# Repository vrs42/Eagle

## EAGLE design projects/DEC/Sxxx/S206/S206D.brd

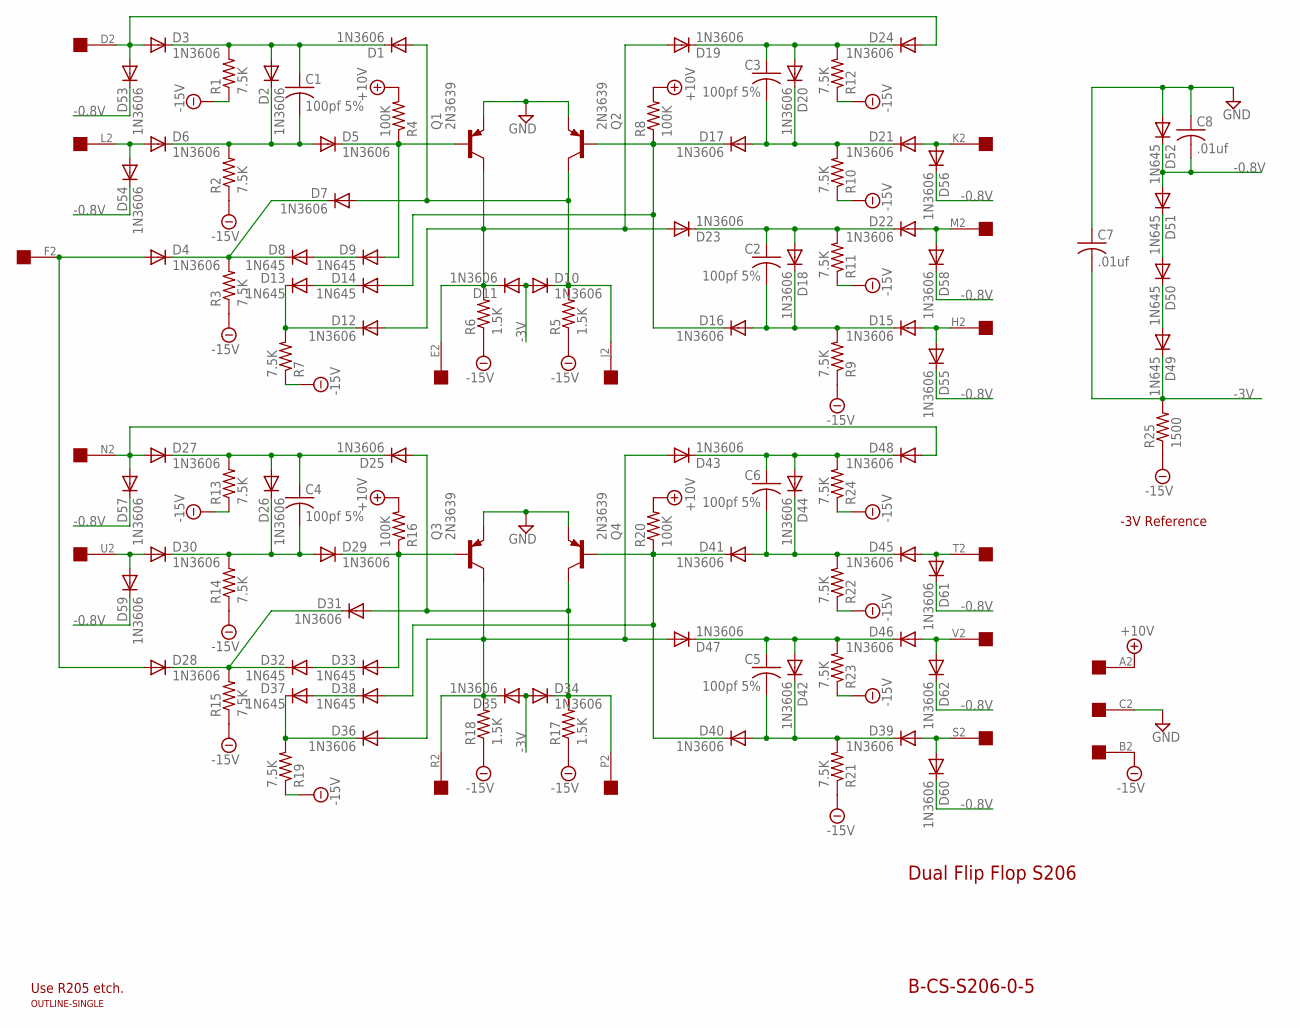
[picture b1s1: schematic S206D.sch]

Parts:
C1, C2, C3, C4, C5, C6: 100pf 5%; C050-025X075
C7, C8: .01uf; C050-025X075
D1, D2, D3, D4, D5, D6, D7, D10, D11, D12, D15, D16, D17, D18, D19, D20, D21, D22, D23, D24, D25, D26, D27, D28, D29, D30, D31, D34, D35, D36, D39, D40, D41, D42, D43, D44, D45, D46, D47, D48, D53, D54, D55, D56, D57, D58, D59, D60, D61, D62: 1N3606; DO35-10
D8, D9, D13, D14, D32, D33, D37, D38, D49, D50, D51, D52: 1N645; DO35-10
Q1, Q2, Q3, Q4: 2N3639; TO39
R1, R2, R3, R7, R9, R10, R11, R12, R13, R14, R15, R19, R21, R22, R23, R24: 7.5K; 0207/10
R4, R8, R16, R20: 100K; 0207/10
R5, R6, R17, R18: 1.5K; 0207/10
R25: 1500; 0207/10
U$1: OUTLINE-SINGLE; SINGLE
U$2: EDGE-1; EDGE-CON1

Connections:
+10V: R4.2, R8.2, R16.2, R20.2, U$2.A2
-0.8V: C8.2, D51.A, D52.C, D53.C, D54.C, D55.C, D56.C, D57.C, D58.C, D59.C, D60.C, D61.C, D62.C
-3V: C7.2, D10.A, D11.A, D34.A, D35.A, D49.C, R25.2
-15V: R1.1, R2.1, R3.1, R5.1, R6.1, R7.1, R9.1, R10.1, R11.1, R12.1, R13.1, R14.1, R15.1, R17.1, R18.1, R19.1, R21.1, R22.1, R23.1, R24.1, R25.1, U$2.B2
E: D11.C, D12.A, D19.A, D23.A, Q1.3 (C), R6.2, U$2.E2
GND: C7.1, C8.1, D52.A, Q1.1 (E), Q2.1 (E), Q3.1 (E), Q4.1 (E), U$2.C2
J: D1.A, D7.A, D10.C, Q2.3 (C), R5.2, U$2.J2
unnamed: C4.1, D25.C, D26.A, D27.C, R13.2
unnamed: C3.1, D19.C, D20.A, D24.C, R12.2
unnamed: C1.2, D2.C, D5.A, D6.C, R2.2
unnamed: D3.A, D24.A, D53.A, U$2.D2
unnamed: D6.A, D54.A, U$2.L2
unnamed: D13.A, D14.C
unnamed: D32.A, D33.C
unnamed: C3.2, D17.A, D20.C, D21.C, R10.2
unnamed: D4.C, D7.C, D8.C, R3.2
unnamed: D4.A, D28.A, U$2.F2
unnamed: D21.A, D56.A, U$2.K2
unnamed: D12.C, D13.C, R7.2
unnamed: D50.A, D51.C
unnamed: D5.C, D9.A, Q1.2 (B), R4.1
unnamed: C4.2, D26.C, D29.A, D30.C, R14.2
unnamed: D49.A, D50.C
unnamed: D14.A, D16.C, D17.C, Q2.2 (B), R8.1
unnamed: D30.A, D59.A, U$2.U2
unnamed: D28.C, D31.C, D32.C, R15.2
unnamed: D29.C, D33.A, Q3.2 (B), R16.1
unnamed: C1.1, D1.C, D2.A, D3.C, R1.2
unnamed: D8.A, D9.C
unnamed: C6.1, D43.C, D44.A, D48.C, R24.2
unnamed: D37.A, D38.C
unnamed: C6.2, D41.A, D44.C, D45.C, R22.2
unnamed: D45.A, D61.A, U$2.T2
unnamed: C2.1, D18.A, D22.C, D23.C, R11.2
unnamed: D38.A, D40.C, D41.C, Q4.2 (B), R20.1
unnamed: D22.A, D58.A, U$2.M2
unnamed: C2.2, D15.C, D16.A, D18.C, R9.2
unnamed: D15.A, D55.A, U$2.H2
unnamed: D36.C, D37.C, R19.2
unnamed: C5.1, D42.A, D46.C, D47.C, R23.2
unnamed: D46.A, D62.A, U$2.V2
unnamed: C5.2, D39.C, D40.A, D42.C, R21.2
unnamed: D39.A, D60.A, U$2.S2
unnamed: D27.A, D48.A, D57.A, U$2.N2
P: D25.A, D31.A, D34.C, Q4.3 (C), R17.2, U$2.P2
R: D35.C, D36.A, D43.A, D47.A, Q3.3 (C), R18.2, U$2.R2

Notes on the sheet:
Dual Flip Flop S206
B-CS-S206-0-5
-3V Reference
Use R205 etch.

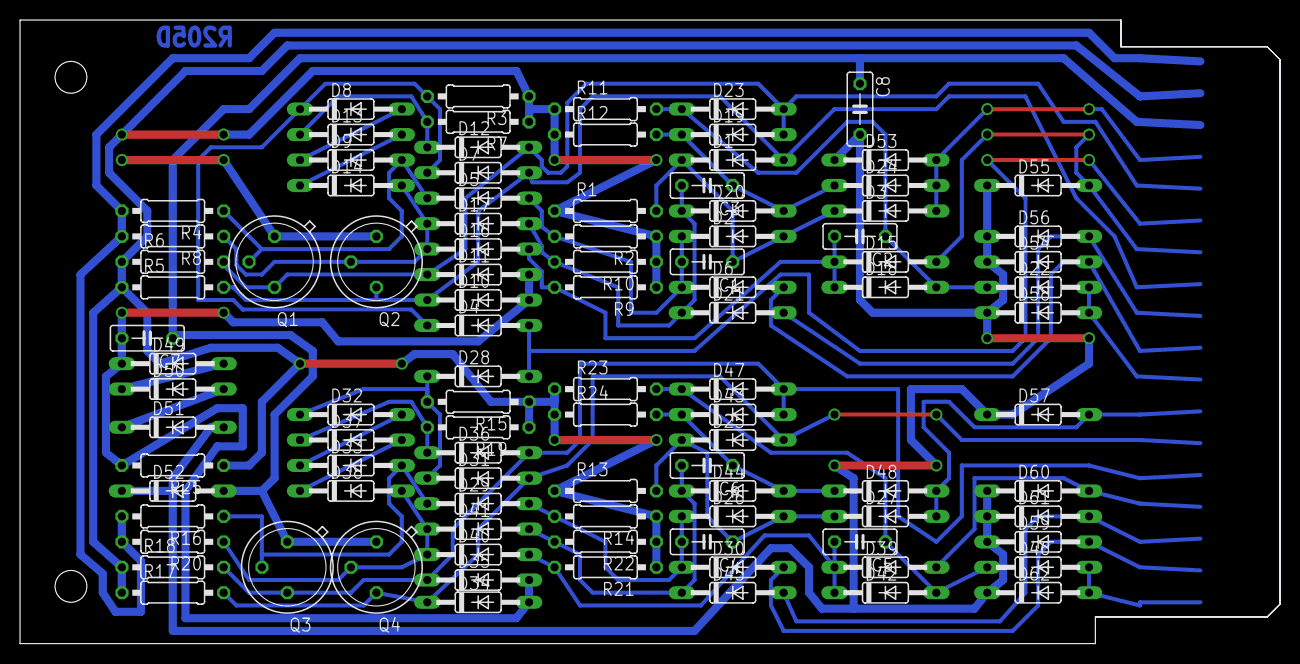
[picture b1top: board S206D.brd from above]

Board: 2 copper layers, 125.7 x 62.2 mm, 101 parts (0 on the bottom side), 46 nets.

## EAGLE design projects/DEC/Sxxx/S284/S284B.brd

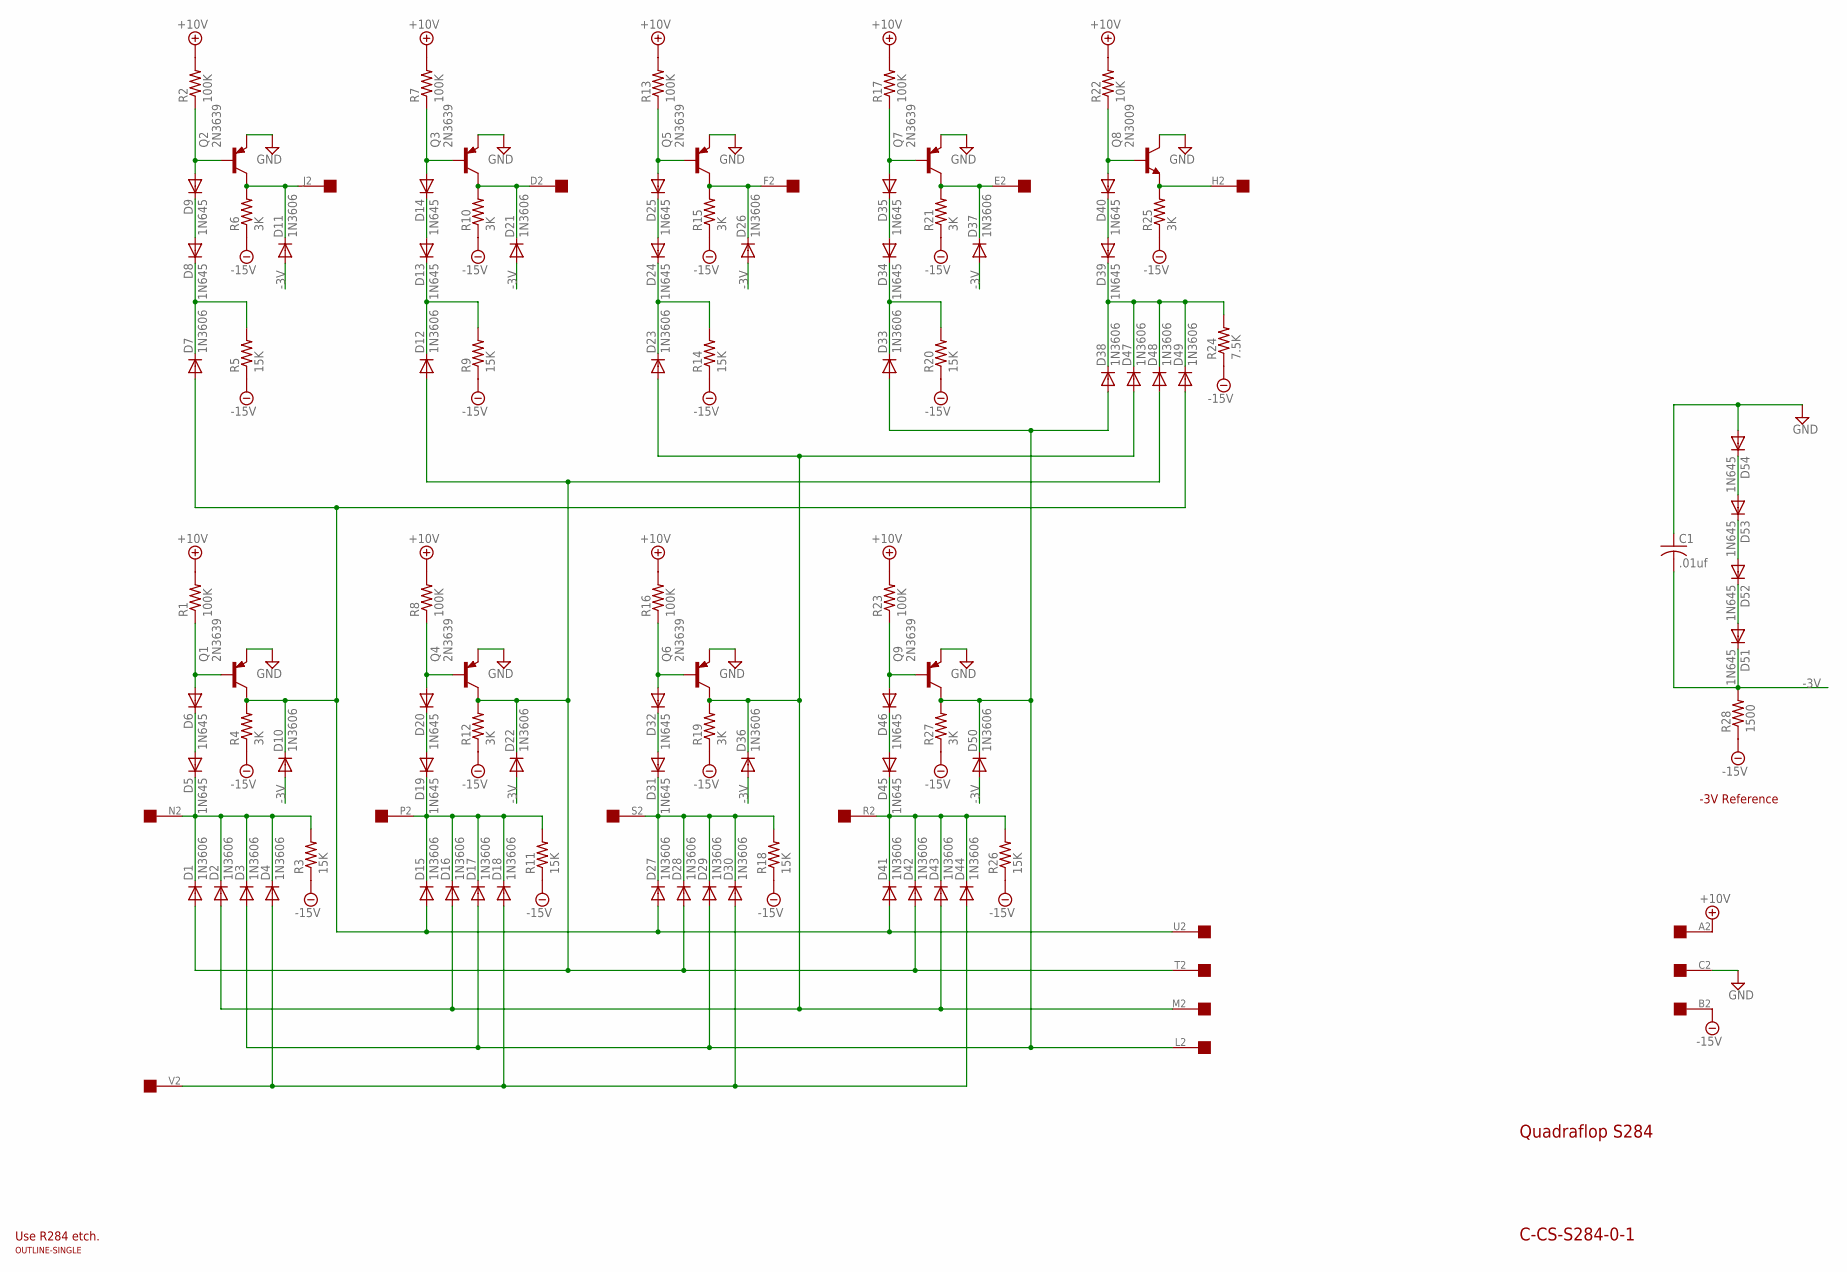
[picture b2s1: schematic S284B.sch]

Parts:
C1: .01uf; C050-025X075
D1, D2, D3, D4, D7, D10, D11, D12, D15, D16, D17, D18, D21, D22, D23, D26, D27, D28, D29, D30, D33, D36, D37, D38, D41, D42, D43, D44, D47, D48, D49, D50: 1N3606; DO35-10
D5, D6, D8, D9, D13, D14, D19, D20, D24, D25, D31, D32, D34, D35, D39, D40, D45, D46, D51, D52, D53, D54: 1N645; DO35-10
Q1, Q2, Q3, Q4, Q5, Q6, Q7, Q9: 2N3639; TO39
Q8: 2N3009; TO5
R1, R2, R7, R8, R13, R16, R17, R23: 100K; 0207/10
R3, R5, R9, R11, R14, R18, R20, R26: 15K; 0207/10
R4, R6, R10, R12, R15, R19, R21, R25, R27: 3K; 0207/10
R22: 10K; 0207/10
R24: 7.5K; 0207/10
R28: 1500; 0207/10
U$1: OUTLINE-SINGLE; SINGLE
U$2: EDGE-1; EDGE-CON1

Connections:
+10V: R1.2, R2.2, R7.2, R8.2, R13.2, R16.2, R17.2, R22.2, R23.2, U$2.A2
-0.8V: D53.A, D54.C
-3V: C1.2, D10.A, D11.A, D21.A, D22.A, D26.A, D36.A, D37.A, D50.A, D51.C, R28.2
-15V: R3.1, R4.1, R5.1, R6.1, R9.1, R10.1, R11.1, R12.1, R14.1, R15.1, R18.1, R19.1, R20.1, R21.1, R24.1, R25.1, R26.1, R27.1, R28.1, U$2.B2
GND: C1.1, D54.A, Q1.1 (E), Q2.1 (E), Q3.1 (E), Q4.1 (E), Q5.1 (E), Q6.1 (E), Q7.1 (E), Q8.3 (C), Q9.1 (E), U$2.C2
L: D3.A, D17.A, D29.A, D33.A, D38.A, D50.C, Q9.3 (C), R27.2, U$2.L2
M: D2.A, D16.A, D23.A, D36.C, D43.A, D47.A, Q6.3 (C), R19.2, U$2.M2
N: D1.C, D2.C, D3.C, D4.C, D5.C, R3.2, U$2.N2
unnamed: D20.A, Q4.2 (B), R8.1
unnamed: D19.A, D20.C
unnamed: D7.A, D10.C, D15.A, D27.A, D41.A, D49.A, Q1.3 (C), R4.2, U$2.U2
unnamed: D7.C, D8.C, R5.2
unnamed: D1.A, D12.A, D22.C, D28.A, D42.A, D48.A, Q4.3 (C), R12.2, U$2.T2
unnamed: D12.C, D13.C, R9.2
unnamed: D13.A, D14.C
unnamed: D8.A, D9.C
unnamed: D21.C, Q3.3 (C), R10.2, U$2.D2
unnamed: D52.A, D53.C
unnamed: D11.C, Q2.3 (C), R6.2, U$2.J2
unnamed: D14.A, Q3.2 (B), R7.1
unnamed: D51.A, D52.C
unnamed: D27.C, D28.C, D29.C, D30.C, D31.C, R18.2, U$2.S2
unnamed: D32.A, Q6.2 (B), R16.1
unnamed: D4.A, D18.A, D30.A, D44.A, U$2.V2
unnamed: D31.A, D32.C
unnamed: D9.A, Q2.2 (B), R2.1
unnamed: D38.C, D39.C, D47.C, D48.C, D49.C, R24.2
unnamed: D23.C, D24.C, R14.2
unnamed: D24.A, D25.C
unnamed: D26.C, Q5.3 (C), R15.2, U$2.F2
unnamed: D25.A, Q5.2 (B), R13.1
unnamed: D41.C, D42.C, D43.C, D44.C, D45.C, R26.2, U$2.R2
unnamed: D6.A, Q1.2 (B), R1.1
unnamed: D46.A, Q9.2 (B), R23.1
unnamed: D5.A, D6.C
unnamed: D45.A, D46.C
unnamed: D40.A, Q8.2 (B), R22.1
unnamed: D33.C, D34.C, R20.2
unnamed: D34.A, D35.C
unnamed: D37.C, Q7.3 (C), R21.2, U$2.E2
unnamed: D35.A, Q7.2 (B), R17.1
unnamed: D39.A, D40.C
unnamed: Q8.1 (E), R25.2, U$2.H2
P: D15.C, D16.C, D17.C, D18.C, D19.C, R11.2, U$2.P2

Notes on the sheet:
Quadraflop S284
C-CS-S284-0-1
-3V Reference
Use R284 etch.

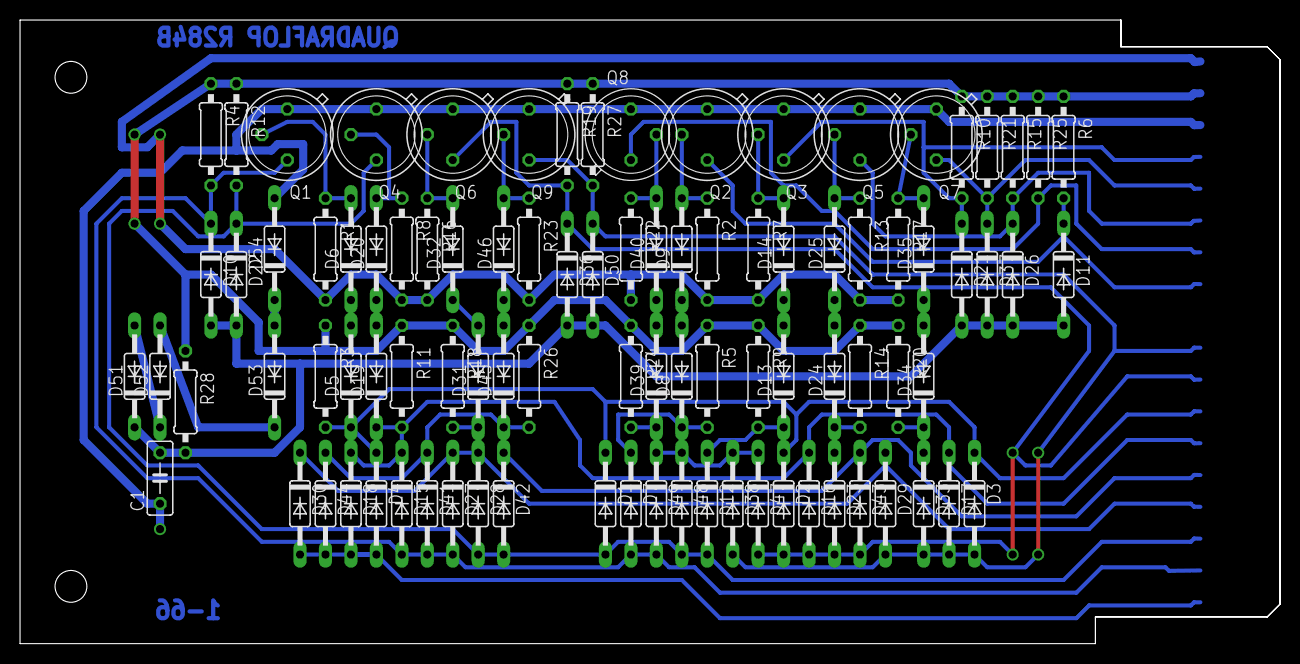
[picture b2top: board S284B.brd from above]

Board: 2 copper layers, 125.7 x 62.2 mm, 94 parts (0 on the bottom side), 44 nets.

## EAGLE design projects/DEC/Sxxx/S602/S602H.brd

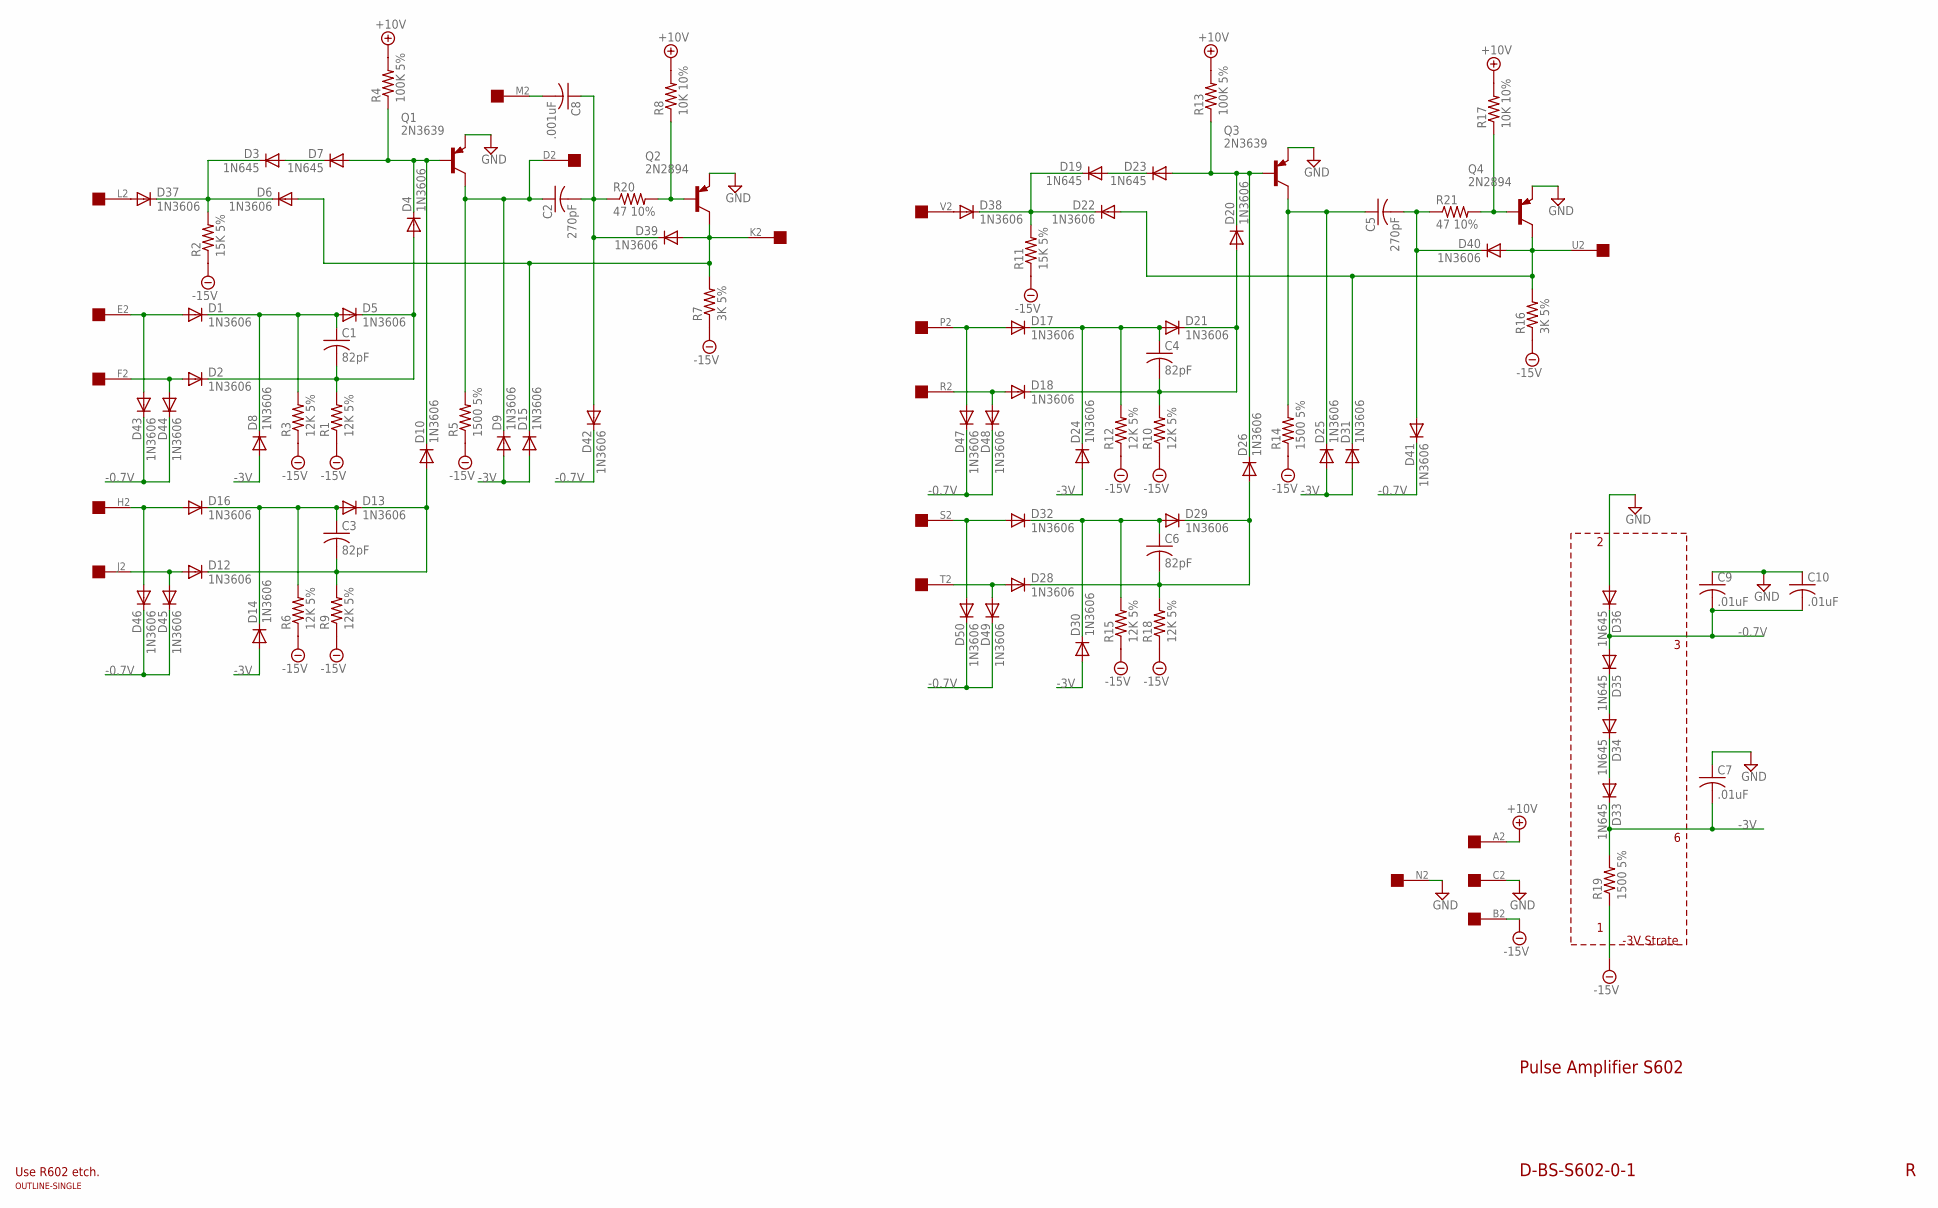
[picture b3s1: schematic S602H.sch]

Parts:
C1, C3, C4, C6: 82pF; C050-025X075
C2, C5: 270pF; C050-025X075
C7: .01uF; C075-032X103
C8: .001uF; C050-025X075
C9, C10: .01uF; C050-025X075
D1, D2, D4, D5, D6, D8, D9, D10, D12, D13, D14, D15, D16, D17, D18, D20, D21, D22, D24, D25, D26, D28, D29, D30, D31, D32, D37, D38, D39, D40, D41, D42, D43, D44, D45, D46, D47, D48, D49, D50: 1N3606; DO35-10
D3, D7, D19, D23, D33, D34, D35, D36: 1N645; DO35-10
Q1, Q3: 2N3639; TO39
Q2, Q4: 2N2894; TO39
R1, R3, R6, R9, R10, R12, R15, R18: 12K 5%; 0207/10
R2, R11: 15K 5%; 0207/10
R4, R13: 100K 5%; 0207/10
R5, R14, R19: 1500 5%; 0207/10
R7, R16: 3K 5%; 0207/10
R8, R17: 10K 10%; 0207/10
R20, R21: 47 10%; 0207/10
U$1: OUTLINE-SINGLE; SINGLE
U$2: EDGE-1; EDGE-CON1

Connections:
+10V: R4.2, R8.2, R13.2, R17.2, U$2.A2
-0.7V: C9.2, C10.2, D35.A, D36.C, D41.C, D42.C, D43.C, D44.C, D45.C, D46.C, D47.C, D48.C, D49.C, D50.C
-3V: C7.2, D8.A, D9.A, D14.A, D15.A, D24.A, D25.A, D30.A, D31.A, D33.C, R19.2
-15V: R1.1, R2.1, R3.1, R5.1, R6.1, R7.1, R9.1, R10.1, R11.1, R12.1, R14.1, R15.1, R16.1, R18.1, R19.1, U$2.B2
GND: C7.1, C9.1, C10.1, D36.A, Q1.1 (E), Q2.1 (E), Q3.1 (E), Q4.1 (E), U$2.C2, U$2.N2
unnamed: D37.A, U$2.L2
unnamed: D3.C, D6.C, D37.C, R2.2
unnamed: D1.A, D43.A, U$2.E2
unnamed: D2.A, D44.A, U$2.F2
unnamed: C1.1, D1.C, D5.A, D8.C, R3.2
unnamed: C1.2, D2.C, D4.A, D5.C, R1.2
unnamed: D3.A, D7.C
unnamed: D34.A, D35.C
unnamed: D33.A, D34.C
unnamed: D4.C, D7.A, D10.C, Q1.2 (B), R4.1
unnamed: C2.1, D9.C, Q1.3 (C), R5.2, U$2.D2
unnamed: C2.2, C8.1, D39.C, D42.A, R20.1
unnamed: Q2.2 (B), R8.1, R20.2
unnamed: D6.A, D15.C, D39.A, Q2.3 (C), R7.2, U$2.K2
unnamed: D16.A, D46.A, U$2.H2
unnamed: D12.A, D45.A, U$2.J2
unnamed: C3.1, D13.A, D14.C, D16.C, R6.2
unnamed: C3.2, D10.A, D12.C, D13.C, R9.2
unnamed: D17.A, D47.A, U$2.P2
unnamed: D18.A, D48.A, U$2.R2
unnamed: C4.1, D17.C, D21.A, D24.C, R12.2
unnamed: C4.2, D18.C, D20.A, D21.C, R10.2
unnamed: D38.A, U$2.V2
unnamed: D19.C, D22.C, D38.C, R11.2
unnamed: D19.A, D23.C
unnamed: D20.C, D23.A, D26.C, Q3.2 (B), R13.1
unnamed: C5.1, D25.C, Q3.3 (C), R14.2
unnamed: C5.2, D40.C, D41.A, R21.1
unnamed: Q4.2 (B), R17.1, R21.2
unnamed: D22.A, D31.C, D40.A, Q4.3 (C), R16.2, U$2.U2
unnamed: D32.A, D50.A, U$2.S2
unnamed: D28.A, D49.A, U$2.T2
unnamed: C6.1, D29.A, D30.C, D32.C, R15.2
unnamed: C6.2, D26.A, D28.C, D29.C, R18.2
unnamed: C8.2, U$2.M2

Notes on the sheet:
Pulse Amplifier S602
D-BS-S602-0-1
-3V Strate
Use R602 etch.

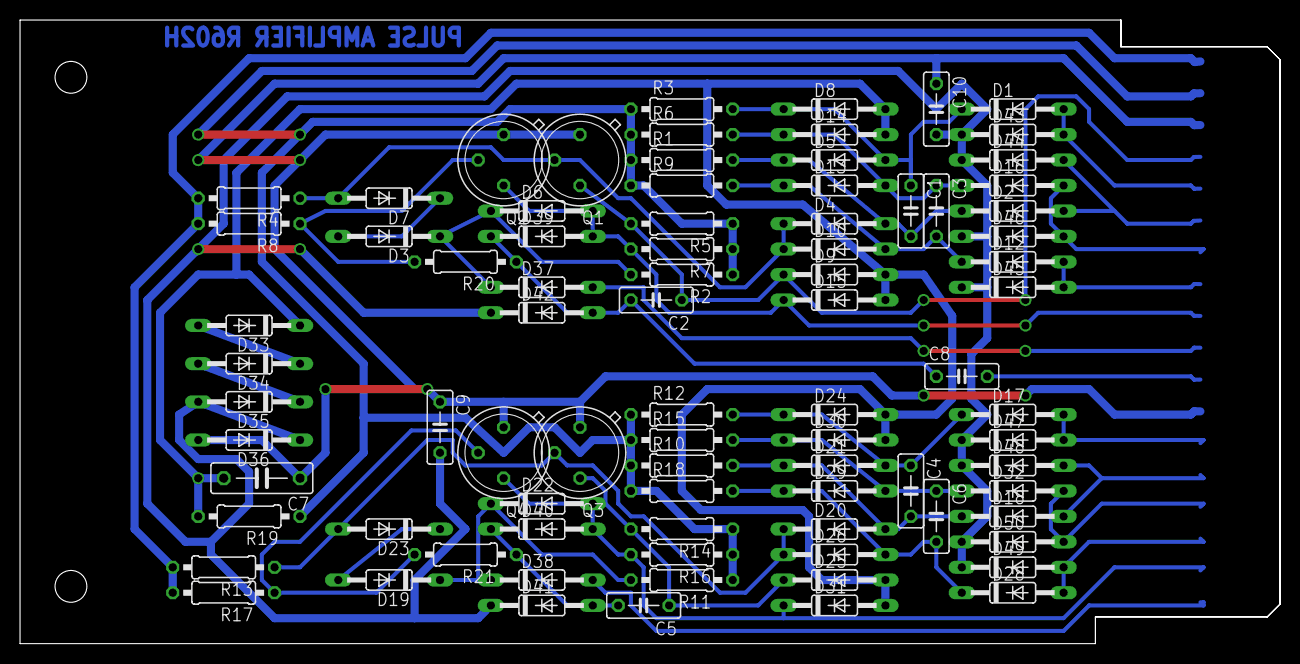
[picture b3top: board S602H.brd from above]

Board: 2 copper layers, 125.7 x 62.2 mm, 85 parts (0 on the bottom side), 40 nets.

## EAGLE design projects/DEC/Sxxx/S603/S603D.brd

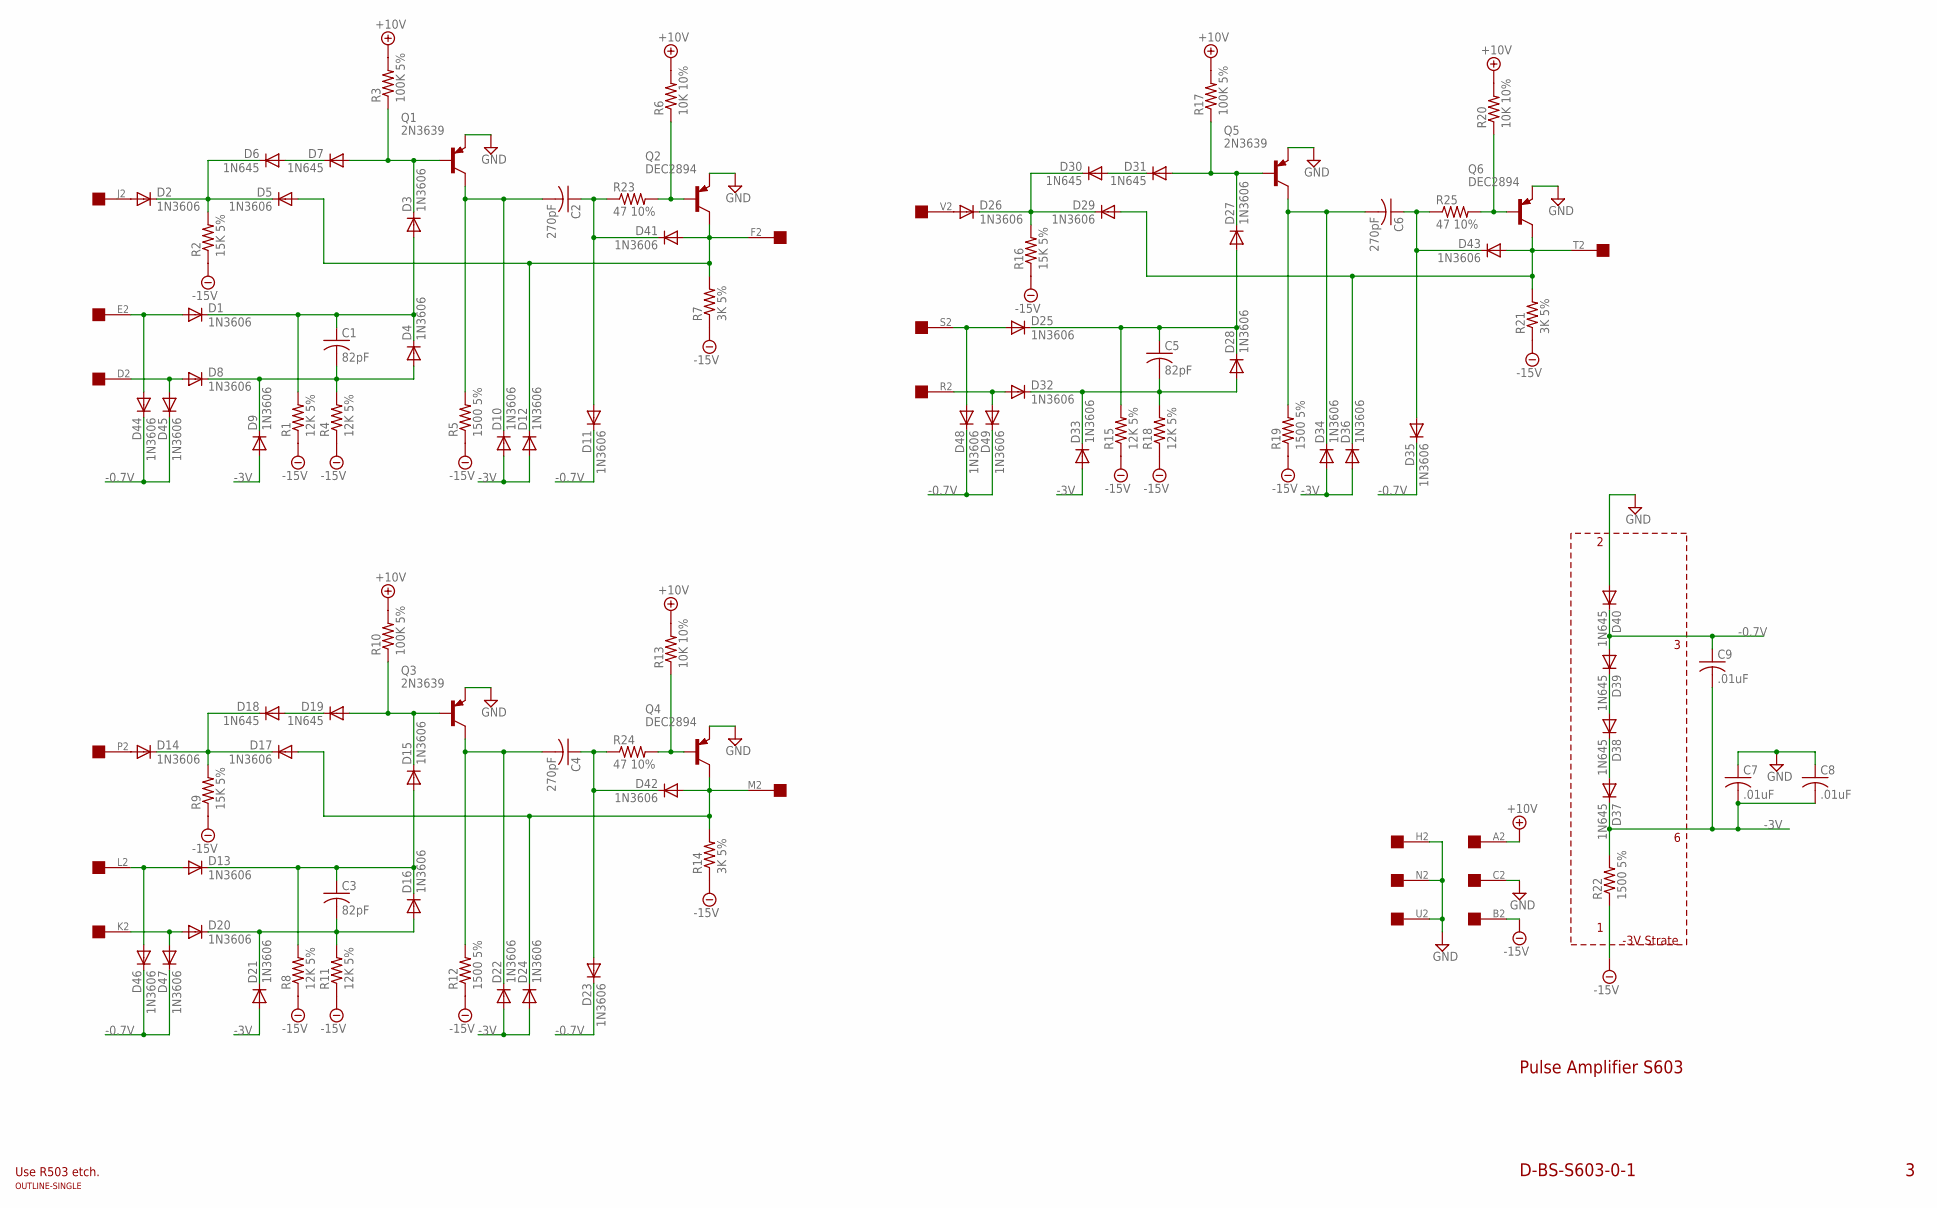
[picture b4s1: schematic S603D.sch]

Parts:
C1, C3, C5: 82pF; C050-025X075
C2, C4, C6: 270pF; C050-025X075
C7, C8, C9: .01uF; C050-025X075
D1, D2, D3, D4, D5, D8, D9, D10, D11, D12, D13, D14, D15, D16, D17, D20, D21, D22, D23, D24, D25, D26, D27, D28, D29, D32, D33, D34, D35, D36, D41, D42, D43, D44, D45, D46, D47, D48, D49: 1N3606; DO35-10
D6, D7, D18, D19, D30, D31, D37, D38, D39, D40: 1N645; DO35-10
Q1, Q3, Q5: 2N3639; TO39
Q2, Q4, Q6: DEC2894; TO39
R1, R4, R8, R11, R15, R18: 12K 5%; 0207/10
R2, R9, R16: 15K 5%; 0207/10
R3, R10, R17: 100K 5%; 0207/10
R5, R12, R19, R22: 1500 5%; 0207/10
R6, R13, R20: 10K 10%; 0207/10
R7, R14, R21: 3K 5%; 0207/10
R23, R24, R25: 47 10%; 0207/10
U$1: OUTLINE-SINGLE; SINGLE
U$2: EDGE-1; EDGE-CON1

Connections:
+10V: R3.2, R6.2, R10.2, R13.2, R17.2, R20.2, U$2.A2
-0.7V: C9.1, D11.C, D23.C, D35.C, D39.A, D40.C, D44.C, D45.C, D46.C, D47.C, D48.C, D49.C
-3V: C7.2, C8.2, C9.2, D9.A, D10.A, D12.A, D21.A, D22.A, D24.A, D33.A, D34.A, D36.A, D37.C, R22.2
-15V: R1.1, R2.1, R4.1, R5.1, R7.1, R8.1, R9.1, R11.1, R12.1, R14.1, R15.1, R16.1, R18.1, R19.1, R21.1, R22.1, U$2.B2
GND: C7.1, C8.1, D40.A, Q1.1 (E), Q2.1 (E), Q3.1 (E), Q4.1 (E), Q5.1 (E), Q6.1 (E), U$2.C2, U$2.H2, U$2.N2, U$2.U2
unnamed: D2.A, U$2.J2
unnamed: D2.C, D5.C, D6.C, R2.2
unnamed: D1.A, D44.A, U$2.E2
unnamed: D8.A, D45.A, U$2.D2
unnamed: C1.1, D1.C, D3.A, D4.C, R1.2
unnamed: C1.2, D4.A, D8.C, D9.C, R4.2
unnamed: D6.A, D7.C
unnamed: D38.A, D39.C
unnamed: D37.A, D38.C
unnamed: D3.C, D7.A, Q1.2 (B), R3.1
unnamed: C2.2, D10.C, Q1.3 (C), R5.2
unnamed: C2.1, D11.A, D41.C, R23.1
unnamed: Q2.2 (B), R6.1, R23.2
unnamed: D5.A, D12.C, D41.A, Q2.3 (C), R7.2, U$2.F2
unnamed: D13.A, D46.A, U$2.L2
unnamed: D20.A, D47.A, U$2.K2
unnamed: C3.1, D13.C, D15.A, D16.C, R8.2
unnamed: C3.2, D16.A, D20.C, D21.C, R11.2
unnamed: D25.A, D48.A, U$2.S2
unnamed: D32.A, D49.A, U$2.R2
unnamed: C5.1, D25.C, D27.A, D28.C, R15.2
unnamed: C5.2, D28.A, D32.C, D33.C, R18.2
unnamed: D26.A, U$2.V2
unnamed: D26.C, D29.C, D30.C, R16.2
unnamed: D30.A, D31.C
unnamed: D27.C, D31.A, Q5.2 (B), R17.1
unnamed: C6.2, D34.C, Q5.3 (C), R19.2
unnamed: C6.1, D35.A, D43.C, R25.1
unnamed: Q6.2 (B), R20.1, R25.2
unnamed: D29.A, D36.C, D43.A, Q6.3 (C), R21.2, U$2.T2
unnamed: D14.A, U$2.P2
unnamed: D14.C, D17.C, D18.C, R9.2
unnamed: D18.A, D19.C
unnamed: D15.C, D19.A, Q3.2 (B), R10.1
unnamed: C4.2, D22.C, Q3.3 (C), R12.2
unnamed: C4.1, D23.A, D42.C, R24.1
unnamed: Q4.2 (B), R13.1, R24.2
unnamed: D17.A, D24.C, D42.A, Q4.3 (C), R14.2, U$2.M2

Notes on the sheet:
Pulse Amplifier S603
D-BS-S603-0-1
-3V Strate
Use R503 etch.

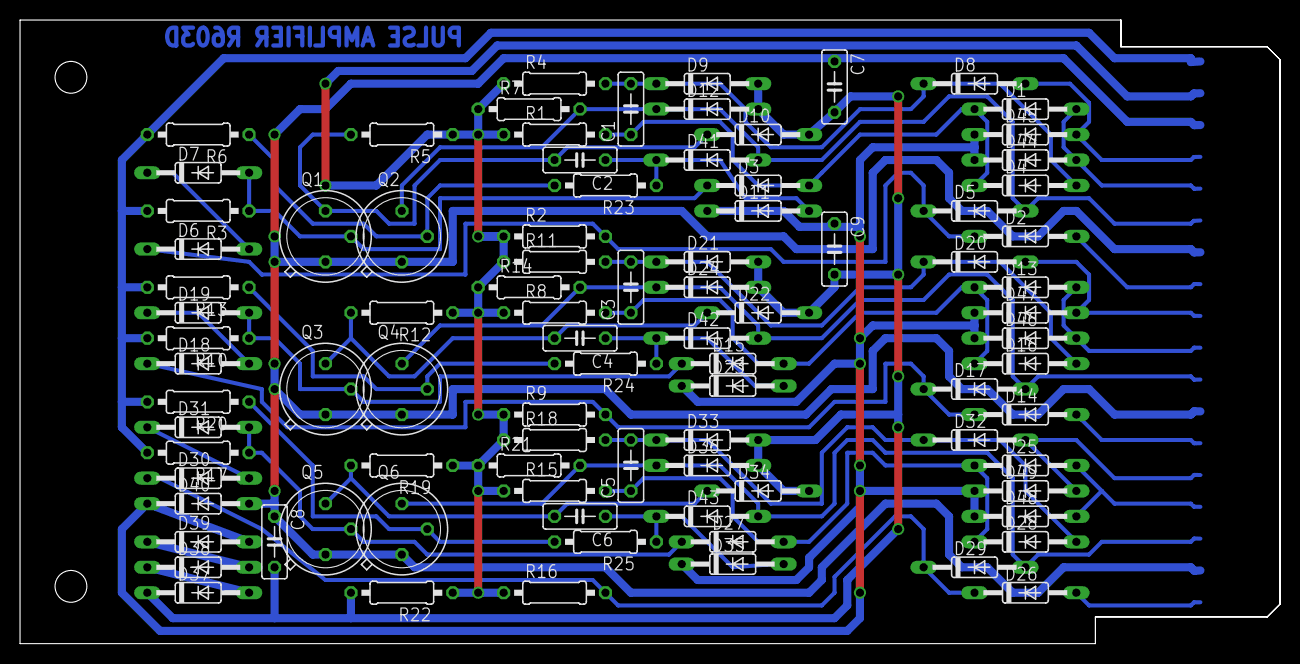
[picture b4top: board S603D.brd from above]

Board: 2 copper layers, 125.7 x 62.2 mm, 91 parts (0 on the bottom side), 43 nets.
